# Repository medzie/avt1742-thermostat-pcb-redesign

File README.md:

# AVT1742 Thermostat - PCB Redesign & Optimization

A hardware cloning and optimization project based on the commercial AVT1742 extended thermostat kit. The core engineering challenge was adapting the original dual-layer design into a strict **single-layer PCB** constraint while systematically improving signal integrity and power routing.

## Key Features & Engineering Challenges

* **Single-Layer Constraint:** Redesigned the entire circuit from scratch to fit a single copper layer (Bottom) to meet strict manufacturing limitations.
* **Solid Ground Pour:** Replaced the original fragmented ground tracks with a continuous copper ground pour. This significantly lowers ground impedance and improves the overall noise immunity of the comparator circuits.
* **Component Placement Optimization:** Relocated decoupling capacitors (C4, C5) significantly closer to the IC power pins (`VCC`/`GND` of LM393 and CD4011) to minimize parasitic inductance and optimize decoupling efficiency.
* **Proven Hardware:** The board was successfully manufactured, soldered, and fully tested. It is 100% operational.

## Technical Overview

* **Core ICs:** LM393 (Low-Power Dual Voltage Comparator), CD4011 (Quad 2-Input NAND Gate)
* **Sensor:** NTC 22kΩ Thermistor
* **Outputs:** 3x Open-Collector outputs with LED status indicators (Too Low, Temp OK, Too High)
* **CAD Software:** Autodesk Eagle

## Repository Structure

* `hardware/` - Eagle CAD schematic (`.sch`) and PCB layout (`.brd`) files.
* `docs/` - Technical documentation, university project report, and original kit datasheets.
* `photos/` - Visual assets, including schematic captures, layout configurations, and hardware testing.

## Gallery & Visualization

### Hardware & PCB Design
Here is the redesigned single-layer PCB layout with the optimized component placement and solid ground pour:

* **Schematic Preview:**

* **PCB Layout & Tracks (Bottom Layer):**

### Assembled & Working Device
Photos of the manufactured, soldered, and fully operational thermostat circuit:

---
*Project developed as part of engineering coursework.*

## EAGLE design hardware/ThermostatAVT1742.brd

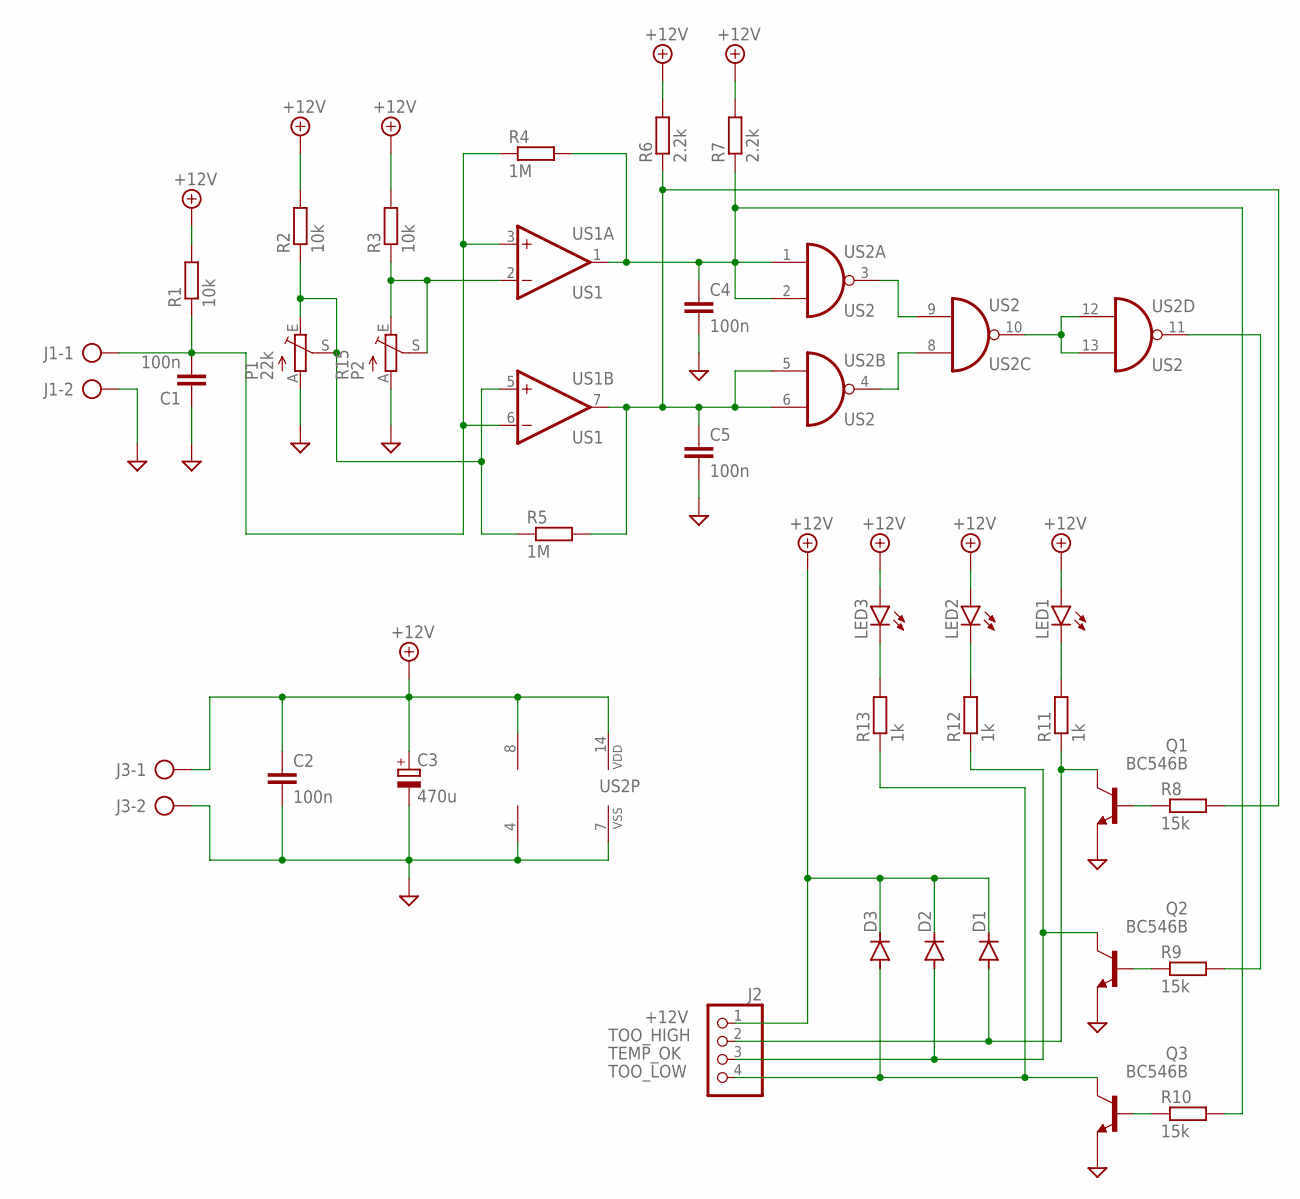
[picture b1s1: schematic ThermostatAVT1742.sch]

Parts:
C1, C2, C4, C5: 100n; C050-025X075
C3: 470u; E3,5-8
D1: red; DO35-10
D2: green; DO35-10
D3: yellow; DO35-10
J1: J1; AK500/2
J2: J2; 1X04
J3: J3; AK500/2
LED1: red; LED5MM
LED2: green; LED5MM
LED3: yellow; LED5MM
P1: 22k; CA6V
Q1, Q2, Q3: BC546B; TO92-EBC
R1, R2, R3: 10k; 0207/10
R4, R5: 1M; 0207/10
R6, R7: 2.2k; 0207/10
R8, R9, R10: 15k; 0207/10
R11, R12, R13: 1k; 0207/10
R15: P2; CA6V
US1: US1; DIL08
US2: US2; DIL14

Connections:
+12V: C2.1, C3.+, D1.C, D2.C, D3.C, J2.1, J3.1, LED1.A, LED2.A, LED3.A, R1.2, R2.2, R3.2, R6.2, R7.2, US1.8 (V+), US2.14 (VDD)
BASE_HIGH: Q1.B, R8.1
BASE_LOW: Q3.B, R10.1
BASE_OK: Q2.B, R9.1
GND: C1.1, C2.2, C3.-, C4.2, C5.2, J1.2, J3.2, P1.A, Q1.E, Q2.E, Q3.E, R15.A, US1.4 (V-), US2.7 (VSS)
L_GREEN: LED2.K (C), R12.2
L_RED: LED1.K (C), R11.2
L_YELLOW: LED3.K (C), R13.2
NTC_SIGNAL: C1.2, J1.1, R1.1, R4.1, US1.3 (+IN), US1.6 (-IN)
OUT_HI_LOGIC: C4.1, R4.2, R7.1, R10.2, US1.1 (OUT), US2.1 (I0), US2.2 (I1)
OUT_LO_LOGIC: C5.1, R5.2, R6.1, R8.2, US1.7 (OUT), US2.5 (I0), US2.6 (I1)
PRESET_HIGH: R3.1, R15.E, R15.S, US1.2 (-IN)
PRESET_LOW: P1.E, P1.S, R2.1, R5.1, US1.5 (+IN)
SYGNAL_A: US2.3 (O), US2.9 (I1)
SYGNAL_B: US2.4 (O), US2.8 (I0)
TEMP_OK: D2.A, J2.3, Q2.C, R12.1
TEMP_OK_FINAL: R9.2, US2.11 (O)
TEMP_OK_NEG: US2.10 (O), US2.12 (I0), US2.13 (I1)
TOO_HIGH: D1.A, J2.2, Q1.C, R11.1
TOO_LOW: D3.A, J2.4, Q3.C, R13.1

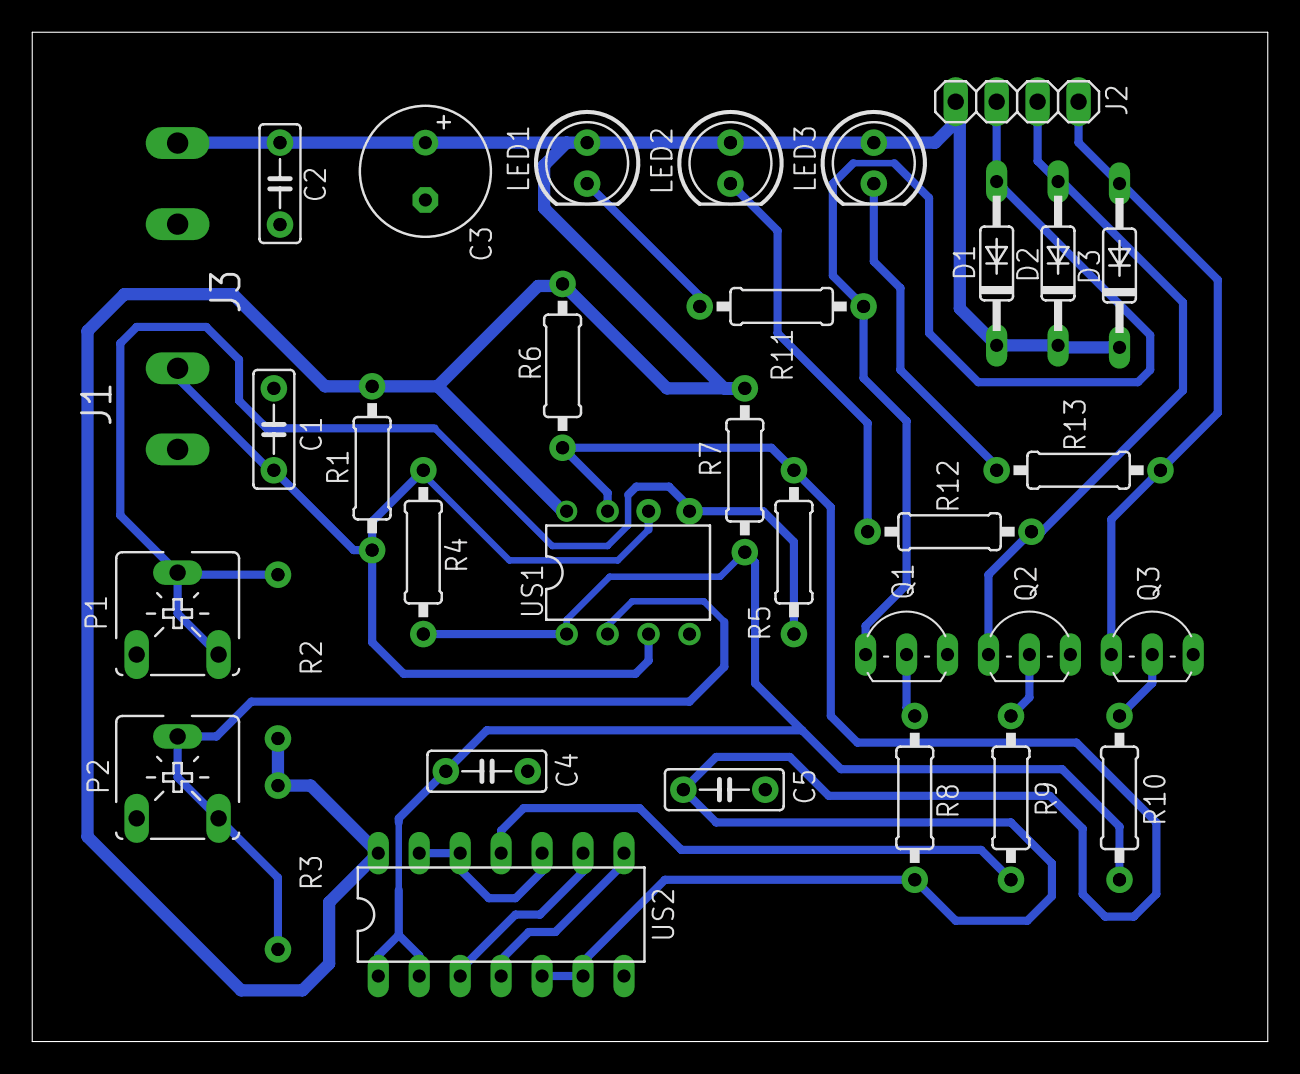
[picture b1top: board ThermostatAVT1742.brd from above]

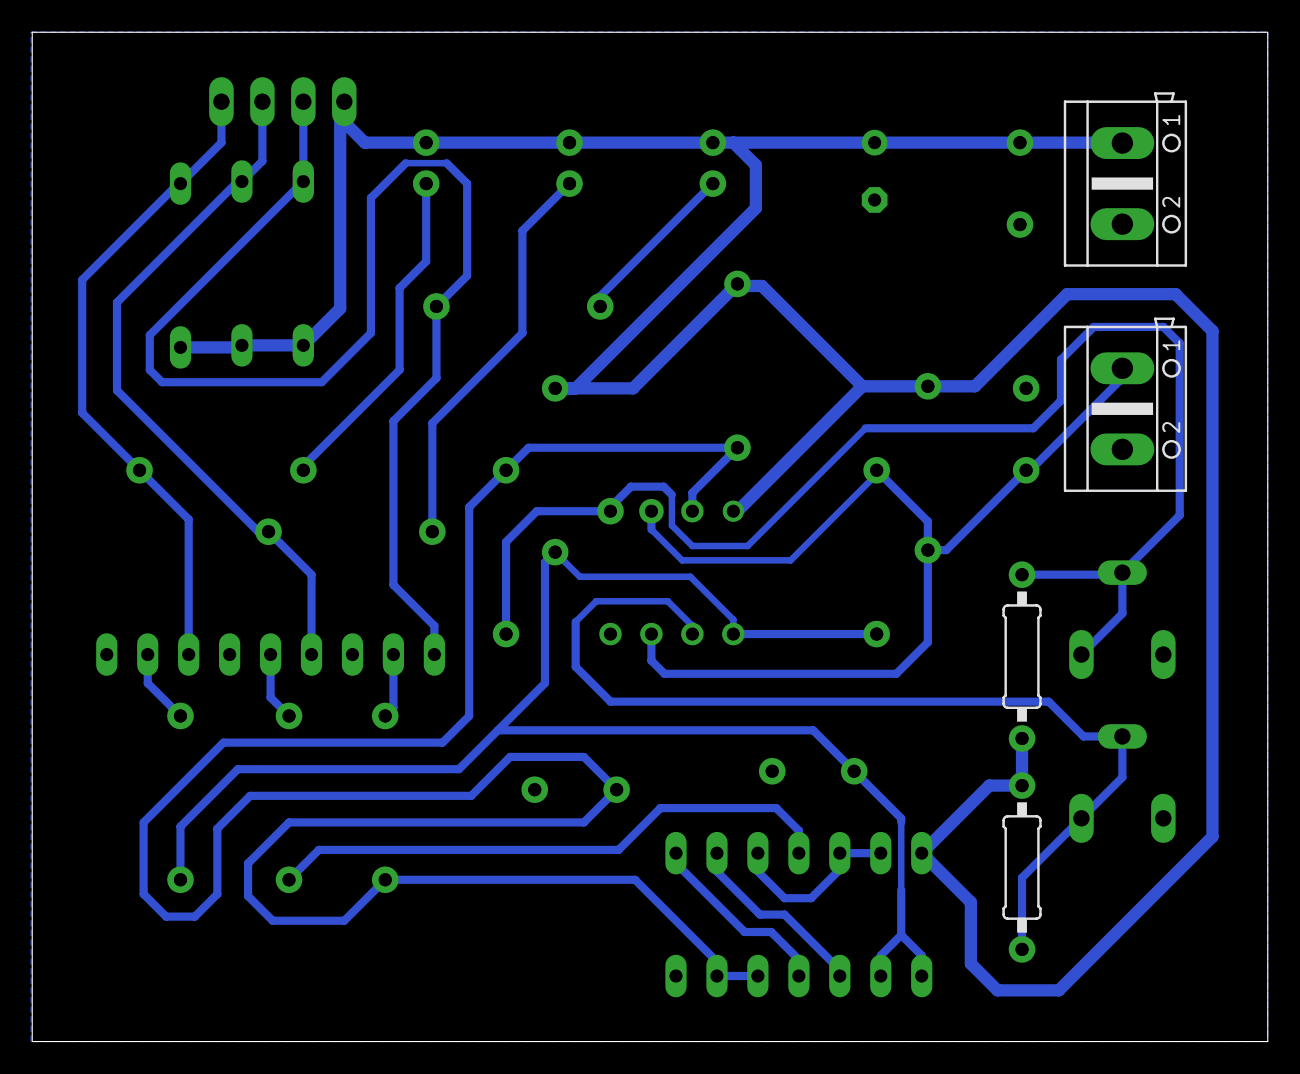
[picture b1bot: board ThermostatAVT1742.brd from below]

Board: 2 copper layers, 76.6 x 62.6 mm, 34 parts (4 on the bottom side), 20 nets.

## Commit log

2026-06-07 docs: Initial commit with single-layer hardware redesign and photos
2026-06-07 Fix formatting and update section headings in README
2026-06-07 Change schematic preview image to PDF format
    Updated schematic preview image format from PNG to PDF.
